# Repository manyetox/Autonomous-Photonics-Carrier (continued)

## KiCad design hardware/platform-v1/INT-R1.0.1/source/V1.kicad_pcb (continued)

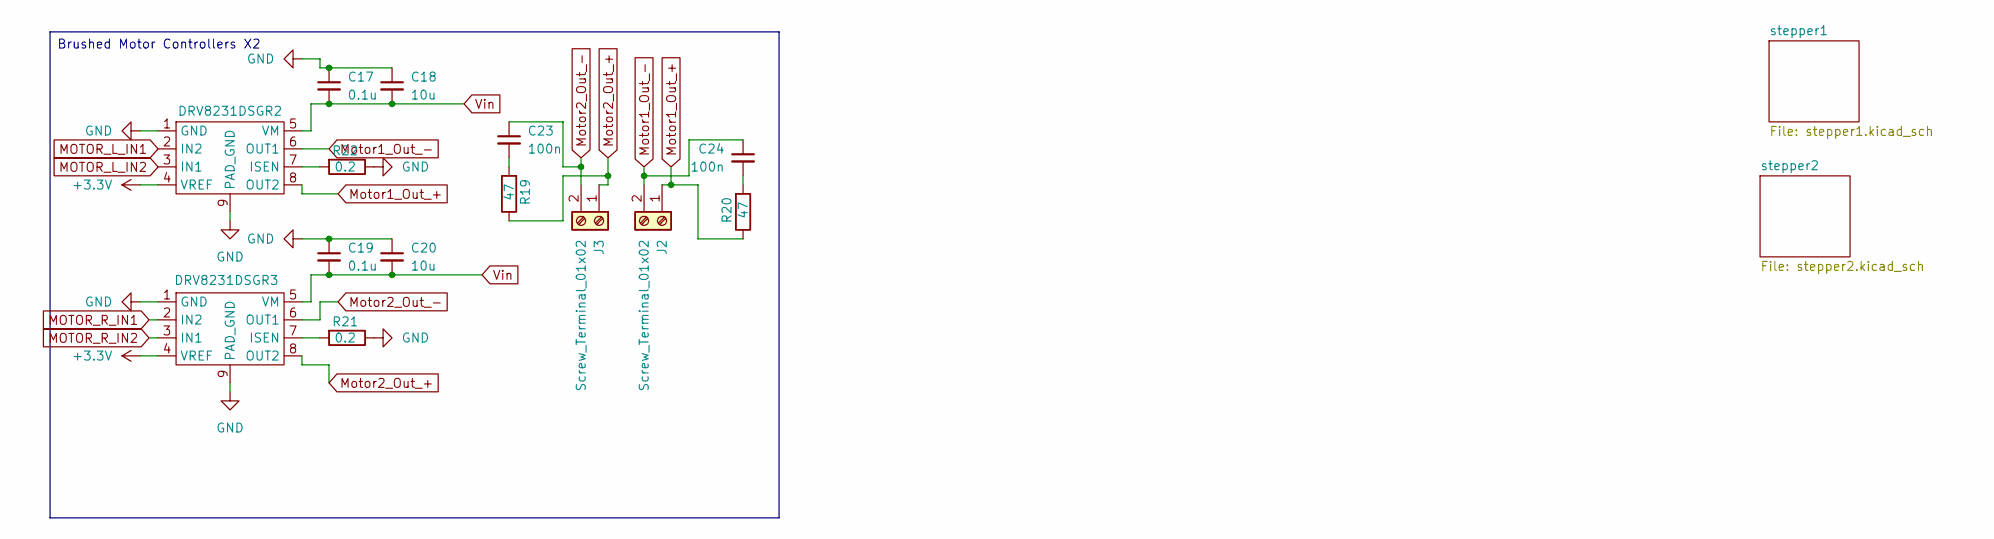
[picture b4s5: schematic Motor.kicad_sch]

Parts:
C17, C19: 0.1u; C_0402_1005Metric_Pad0.74x0.62mm_HandSolder; LCSC Part # C14663
C18, C20: 10u; C_0603_1608Metric_Pad1.08x0.95mm_HandSolder; LCSC Part # C5464883
C23, C24: 100n; C_0402_1005Metric_Pad0.74x0.62mm_HandSolder; LCSC Part # C14663
DRV8231DSGR2, DRV8231DSGR3: HSOP-8-1EP_3.9x4.9mm_P1.27mm_EP2.41x3.1mm_ThermalVias; LCSC Part # C3681197
J2: Screw_Terminal_01x02; PinHeader_2x01_P2.54mm_Vertical
J3: Screw_Terminal_01x02; PinSocket_2x01_P2.54mm_Vertical
R19, R20: 47; R_1206_3216Metric_Pad1.30x1.75mm_HandSolder; LCSC Part # C23182
R21, R22: 0.2; R_2512_6332Metric_Pad1.40x3.35mm_HandSolder; LCSC Part # C23182

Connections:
GND: C17.1, C18.1, C19.1, C20.1, DRV8231DSGR2.1 (GND), DRV8231DSGR2.9 (PAD_GND), DRV8231DSGR3.1 (GND), DRV8231DSGR3.9 (PAD_GND), R21.1, R22.1; also elsewhere on the board
MOTOR_L_IN1: DRV8231DSGR2.2 (IN2); also elsewhere on the board
MOTOR_L_IN2: DRV8231DSGR2.3 (IN1); also elsewhere on the board
MOTOR_R_IN1: DRV8231DSGR3.2 (IN2); also elsewhere on the board
MOTOR_R_IN2: DRV8231DSGR3.3 (IN1); also elsewhere on the board
Motor1_Out_+: DRV8231DSGR2.8 (OUT2), J2.1, R20.1
Motor1_Out_-: C24.1, DRV8231DSGR2.6 (OUT1), J2.2
Motor2_Out_+: DRV8231DSGR3.8 (OUT2), J3.1, R19.1
Motor2_Out_-: C23.1, DRV8231DSGR3.6 (OUT1), J3.2
unnamed: C23.2, R19.2
unnamed: C24.2, R20.2
unnamed: DRV8231DSGR2.7 (ISEN), R22.2
unnamed: DRV8231DSGR3.7 (ISEN), R21.2
PS1: DRV8231DSGR2.4 (VREF), DRV8231DSGR3.4 (VREF); also elsewhere on the board
Vin: C17.2, C18.2, C19.2, C20.2, DRV8231DSGR2.5 (VM), DRV8231DSGR3.5 (VM); also elsewhere on the board

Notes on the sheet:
Brushed Motor Controllers X2

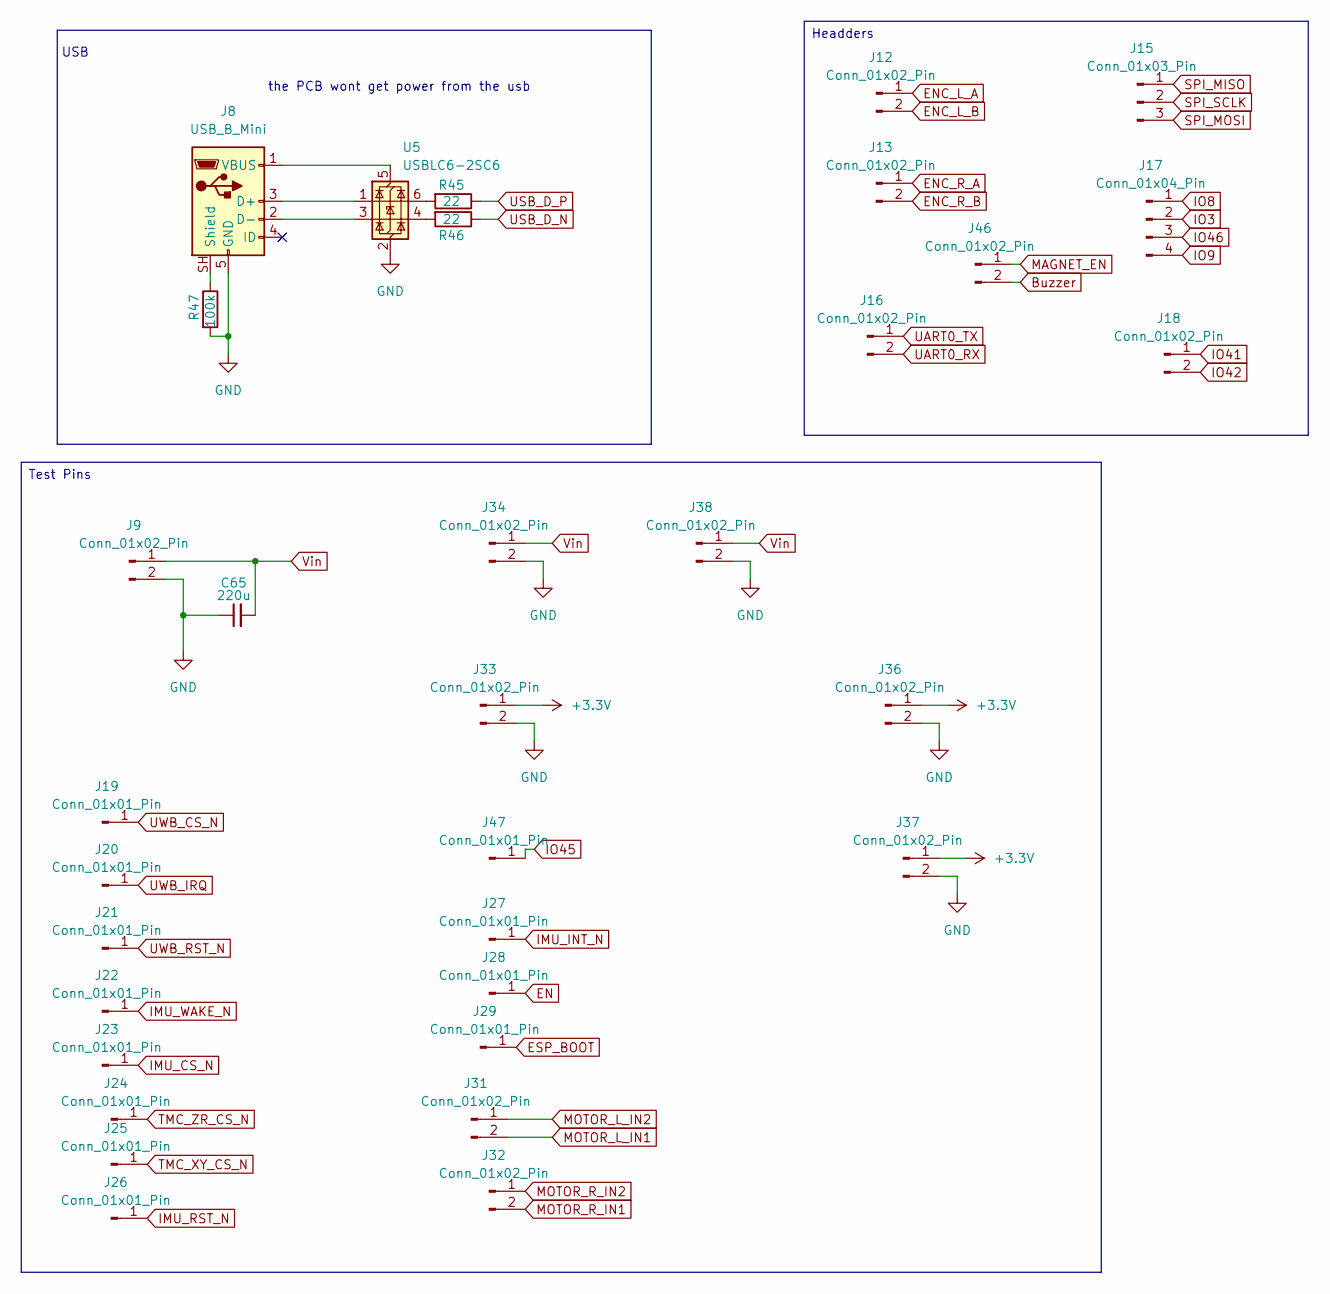
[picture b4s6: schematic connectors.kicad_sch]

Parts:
C65: 220u; C_Radial_D10.0mm_H12.5mm_P5.00mm; LCSC Part # C14663
J8: USB_B_Mini; USB_Mini-B_Wuerth_65100516121_Horizontal
J9, J12, J13, J16, J18, J31, J32, J33, J34, J36, J37, J46: Conn_01x02_Pin; PinHeader_1x02_P1.00mm_Vertical
J15: Conn_01x03_Pin; PinHeader_1x03_P1.00mm_Vertical
J17: Conn_01x04_Pin; PinHeader_1x04_P1.00mm_Vertical
J19, J20, J21, J22, J23, J24, J25, J26, J27, J28, J29, J47: Conn_01x01_Pin; SolderWirePad_1x01_SMD_1x2mm
J38: Conn_01x02_Pin; PinHeader_1x02_P2.54mm_Vertical
R45, R46: 22; R_0402_1005Metric_Pad0.72x0.64mm_HandSolder; LCSC Part # C4211
R47: 100k; R_0402_1005Metric_Pad0.72x0.64mm_HandSolder; LCSC Part # C4211
U5: USBLC6-2SC6; SOT-23-6

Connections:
Buzzer: J46.2; also elsewhere on the board
EN: J28.1 (Pin_1_1); also elsewhere on the board
ENC_L_A: J12.1; also elsewhere on the board
ENC_L_B: J12.2; also elsewhere on the board
ENC_R_A: J13.1; also elsewhere on the board
ENC_R_B: J13.2; also elsewhere on the board
ESP_BOOT: J29.1 (Pin_1_1); also elsewhere on the board
GND: C65.1, J8.5 (GND), J9.2, J33.2, J34.2, J36.2, J37.2, J38.2, R47.2, U5.2 (GND); also elsewhere on the board
IMU_CS_N: J23.1 (Pin_1_1); also elsewhere on the board
IMU_INT_N: J27.1 (Pin_1_1); also elsewhere on the board
IMU_RST_N: J26.1 (Pin_1_1); also elsewhere on the board
IMU_WAKE_N: J22.1 (Pin_1_1); also elsewhere on the board
IO3: J17.2; also elsewhere on the board
IO8: J17.1; also elsewhere on the board
IO9: J17.4; also elsewhere on the board
IO41: J18.1; also elsewhere on the board
IO42: J18.2; also elsewhere on the board
IO45: J47.1 (Pin_1_1); also elsewhere on the board
IO46: J17.3; also elsewhere on the board
MAGNET_EN: J46.1; also elsewhere on the board
MOTOR_L_IN1: J31.2; also elsewhere on the board
MOTOR_L_IN2: J31.1; also elsewhere on the board
MOTOR_R_IN1: J32.2; also elsewhere on the board
MOTOR_R_IN2: J32.1; also elsewhere on the board
unnamed: J8.3 (D+), U5.1 (I/O1)
unnamed: J8.2 (D-), U5.3 (I/O2)
unnamed: J8.SH (Shield), R47.1
unnamed: J8.1 (VBUS), U5.5 (VBUS)
unnamed: R45.2, U5.6 (I/O1)
unnamed: R46.2, U5.4 (I/O2)
PS1: J33.1, J36.1, J37.1; also elsewhere on the board
SPI_MISO: J15.1; also elsewhere on the board
SPI_MOSI: J15.3; also elsewhere on the board
SPI_SCLK: J15.2; also elsewhere on the board
TMC_XY_CS_N: J25.1 (Pin_1_1); also elsewhere on the board
TMC_ZR_CS_N: J24.1 (Pin_1_1); also elsewhere on the board
UART0_RX: J16.2; also elsewhere on the board
UART0_TX: J16.1; also elsewhere on the board
USB_D_N: R46.1; also elsewhere on the board
USB_D_P: R45.1; also elsewhere on the board
UWB_CS_N: J19.1 (Pin_1_1); also elsewhere on the board
UWB_IRQ: J20.1 (Pin_1_1); also elsewhere on the board
UWB_RST_N: J21.1 (Pin_1_1); also elsewhere on the board
Vin: C65.2, J9.1, J34.1, J38.1; also elsewhere on the board

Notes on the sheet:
USB
the PCB wont get power from the usb
Test Pins
Headders

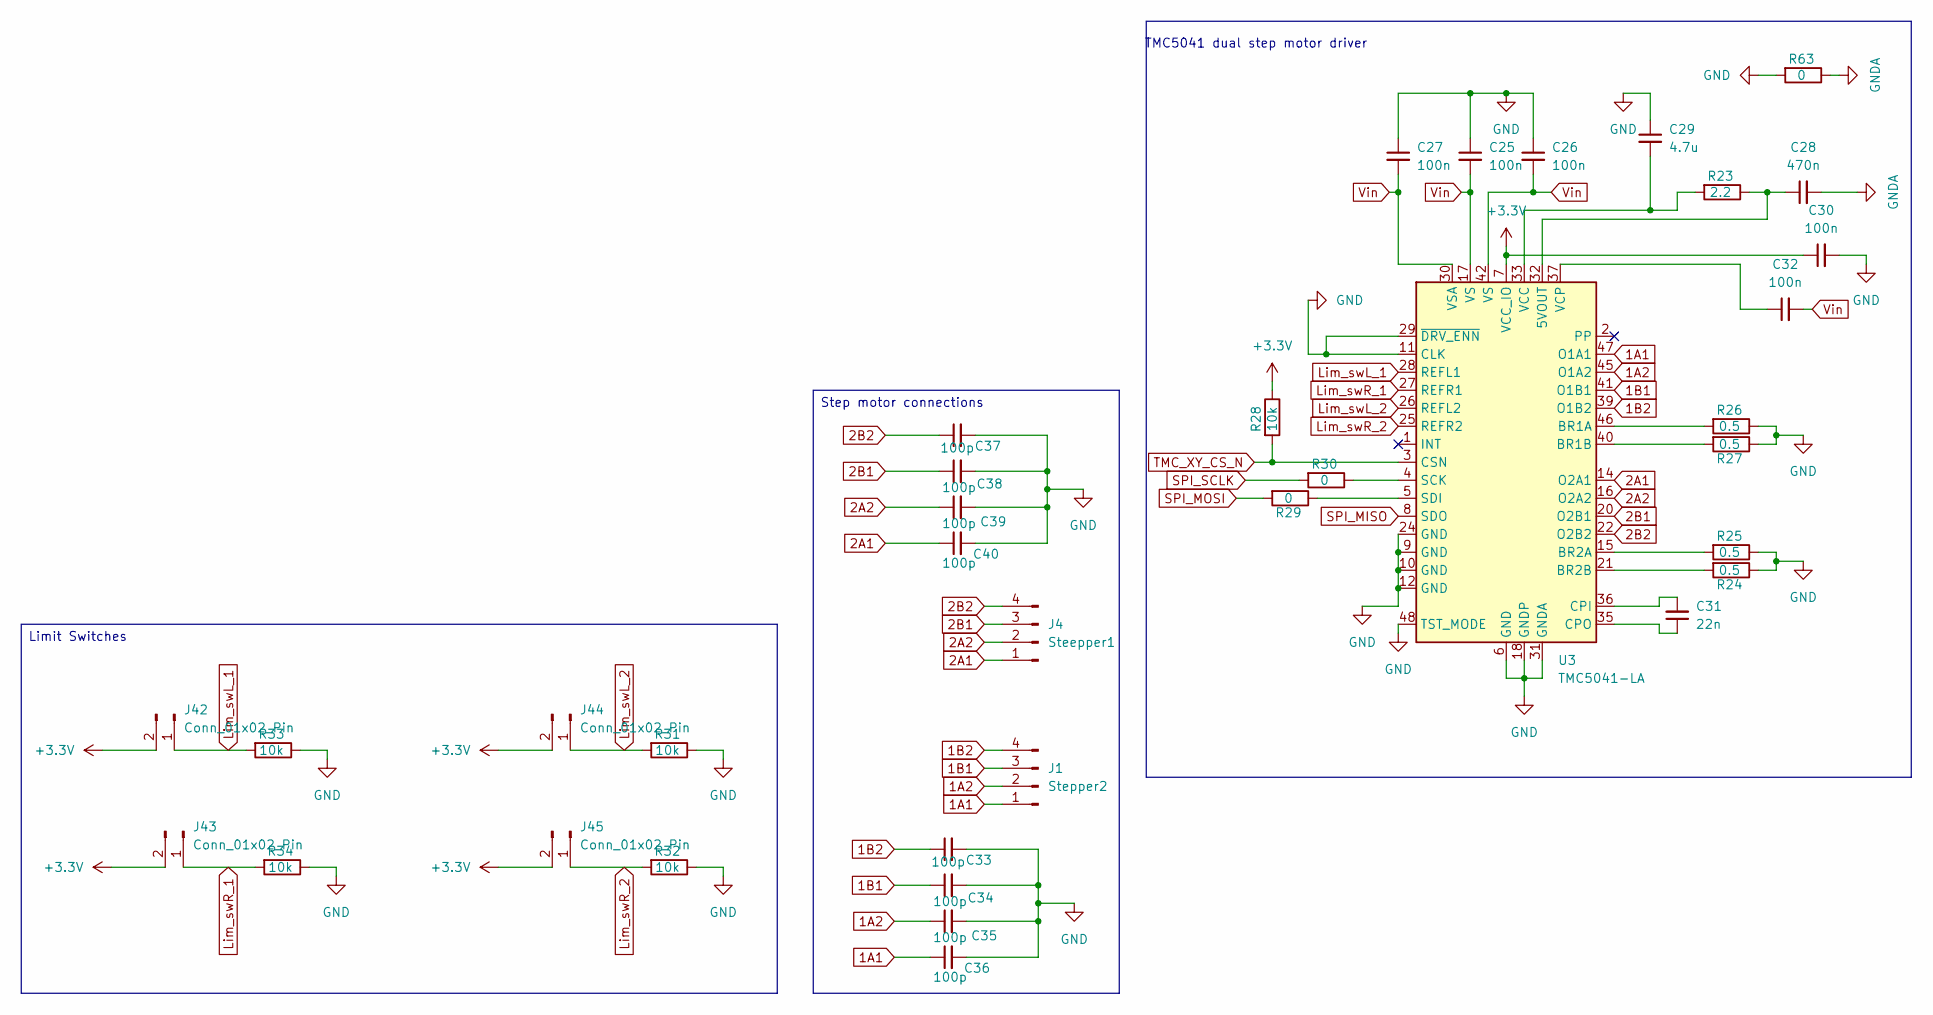
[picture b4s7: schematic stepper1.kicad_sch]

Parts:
C25, C26, C27, C30, C32: 100n; C_0402_1005Metric_Pad0.74x0.62mm_HandSolder; LCSC Part # C14663
C28: 470n; C_0402_1005Metric_Pad0.74x0.62mm_HandSolder; LCSC Part # C14663
C29: 4.7u; C_0402_1005Metric_Pad0.74x0.62mm_HandSolder; LCSC Part # C14663
C31: 22n; C_0402_1005Metric_Pad0.74x0.62mm_HandSolder; LCSC Part # C14663
C33, C34, C35, C36, C37, C38, C39, C40: 100p; C_0402_1005Metric_Pad0.74x0.62mm_HandSolder; LCSC Part # C14663
J1: Stepper2; PinHeader_1x04_P1.00mm_Vertical
J4: Steepper1; PinHeader_1x04_P1.00mm_Vertical
J42, J43, J44, J45: Conn_01x02_Pin; PinHeader_1x02_P1.00mm_Vertical
R23: 2.2; R_0402_1005Metric_Pad0.72x0.64mm_HandSolder; LCSC Part # C23182
R24, R25, R26, R27: 0.5; R_1206_3216Metric_Pad1.30x1.75mm_HandSolder; LCSC Part # C23182
R28, R31, R32, R33, R34: 10k; R_0402_1005Metric_Pad0.72x0.64mm_HandSolder; LCSC Part # C23182
R29, R30, R63: 0; R_0402_1005Metric_Pad0.72x0.64mm_HandSolder; LCSC Part # C23182
U3: TMC5041-LA; QFN-48-1EP_7x7mm_P0.5mm_EP5.3x5.3mm_ThermalVias

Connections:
1A1: C36.1, J1.1, U3.47 (O1A1)
1A2: C35.1, J1.2, U3.45 (O1A2)
1B1: C34.1, J1.3, U3.41 (O1B1)
1B2: C33.1, J1.4, U3.39 (O1B2)
2A1: C40.1, J4.1, U3.14 (O2A1)
2A2: C39.1, J4.2, U3.16 (O2A2)
2B1: C38.1, J4.3, U3.20 (O2B1)
2B2: C37.1, J4.4, U3.22 (O2B2)
GND: C25.1, C26.1, C27.1, C29.1, C30.2, C33.2, C34.2, C35.2, C36.2, C37.2, C38.2, C39.2, C40.2, R24.1, R25.1, R26.1, R27.1, R31.1, R32.1, R33.1, R34.1, R63.2, U3.6 (GND), U3.9 (GND), U3.10 (GND), U3.11 (CLK), U3.12 (GND), U3.13 (nc), U3.18 (GNDP), U3.23 (nc), U3.24 (GND), U3.29 (~DRV_ENN), U3.31 (GNDA), U3.34 (GND), U3.38 (nc), U3.43 (GNDP), U3.48 (TST_MODE), U3.49 (EP_GND); also elsewhere on the board
GNDA: C28.2, R63.1; also elsewhere on the board
Lim_swL_1: J42.1, R33.2, U3.28 (REFL1)
Lim_swL_2: J44.1, R31.2, U3.26 (REFL2)
Lim_swR_1: J43.1, R34.2, U3.27 (REFR1)
Lim_swR_2: J45.1, R32.2, U3.25 (REFR2)
unnamed: C28.1, R23.1, U3.32 (5VOUT)
unnamed: R26.2, U3.46 (BR1A)
unnamed: R27.2, U3.40 (BR1B)
unnamed: R25.2, U3.15 (BR2A)
unnamed: R24.2, U3.21 (BR2B)
unnamed: C31.2, U3.36 (CPI)
unnamed: C31.1, U3.35 (CPO)
unnamed: R30.1, U3.4 (SCK)
unnamed: R29.1, U3.5 (SDI)
unnamed: C29.2, R23.2, U3.33 (VCC)
unnamed: C32.1, U3.37 (VCP)
PS1: C30.1, J42.2, J43.2, J44.2, J45.2, R28.1, U3.7 (VCC_IO); also elsewhere on the board
SPI_MISO: U3.8 (SDO); also elsewhere on the board
SPI_MOSI: R29.2; also elsewhere on the board
SPI_SCLK: R30.2; also elsewhere on the board
TMC_XY_CS_N: R28.2, U3.3 (CSN); also elsewhere on the board
Vin: C25.2, C26.2, C27.2, C32.2, U3.17 (VS), U3.19 (VS), U3.30 (VSA), U3.42 (VS), U3.44 (VS); also elsewhere on the board

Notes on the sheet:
TMC5041 dual step motor driver
Limit Switches
Step motor connections

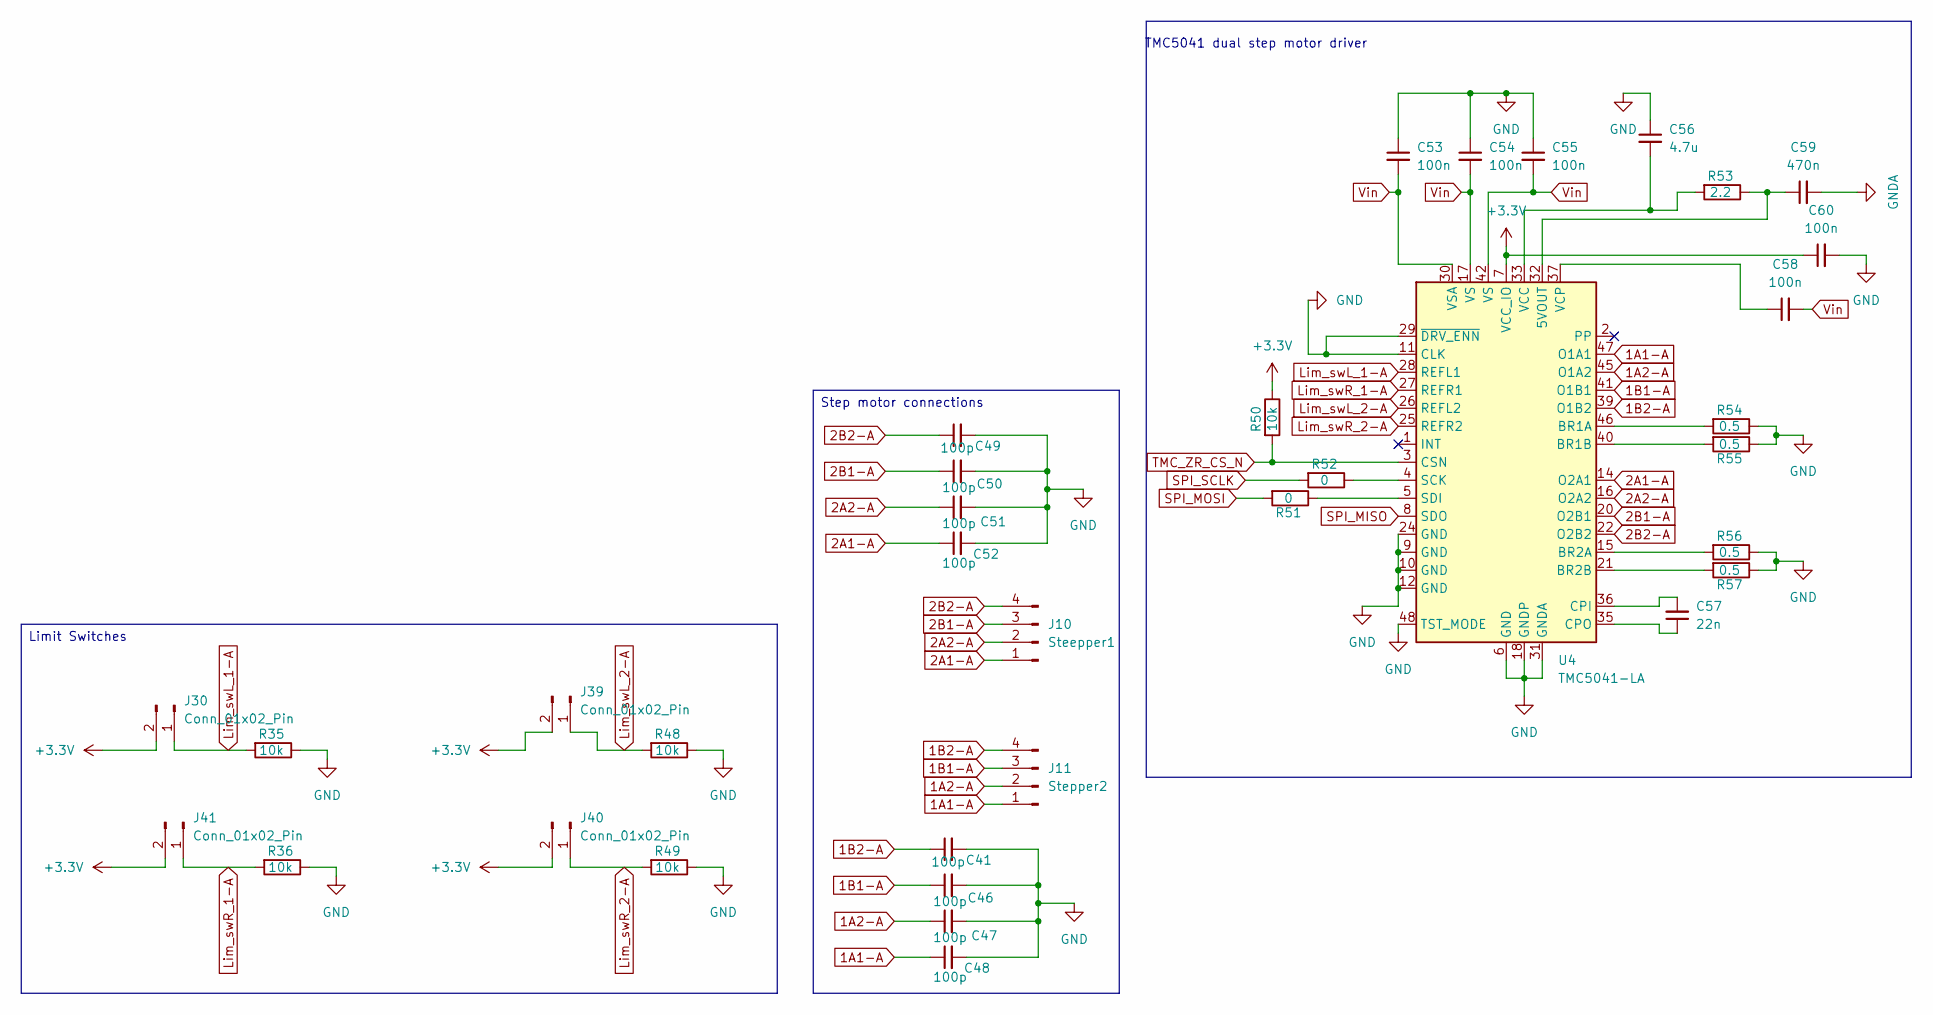
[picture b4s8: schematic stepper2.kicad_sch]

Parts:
C41, C46, C47, C48, C49, C50, C51, C52: 100p; C_0402_1005Metric_Pad0.74x0.62mm_HandSolder; LCSC Part # C14663
C53, C54, C55, C58, C60: 100n; C_0402_1005Metric_Pad0.74x0.62mm_HandSolder; LCSC Part # C14663
C56: 4.7u; C_0402_1005Metric_Pad0.74x0.62mm_HandSolder; LCSC Part # C14663
C57: 22n; C_0402_1005Metric_Pad0.74x0.62mm_HandSolder; LCSC Part # C14663
C59: 470n; C_0402_1005Metric_Pad0.74x0.62mm_HandSolder; LCSC Part # C14663
J10: Steepper1; PinHeader_1x04_P1.00mm_Vertical
J11: Stepper2; PinHeader_1x04_P1.00mm_Vertical
J30, J39, J40, J41: Conn_01x02_Pin; PinHeader_1x02_P1.00mm_Vertical
R35, R36, R48, R49, R50: 10k; R_0402_1005Metric_Pad0.72x0.64mm_HandSolder; LCSC Part # C23182
R51, R52: 0; R_0402_1005Metric_Pad0.72x0.64mm_HandSolder; LCSC Part # C23182
R53: 2.2; R_0402_1005Metric_Pad0.72x0.64mm_HandSolder; LCSC Part # C23182
R54, R55, R56, R57: 0.5; R_1206_3216Metric_Pad1.30x1.75mm_HandSolder; LCSC Part # C23182
U4: TMC5041-LA; QFN-48-1EP_7x7mm_P0.5mm_EP5.3x5.3mm_ThermalVias

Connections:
1A1-A: C48.1, J11.1, U4.47 (O1A1)
1A2-A: C47.1, J11.2, U4.45 (O1A2)
1B1-A: C46.1, J11.3, U4.41 (O1B1)
1B2-A: C41.1, J11.4, U4.39 (O1B2)
2A1-A: C52.1, J10.1, U4.14 (O2A1)
2A2-A: C51.1, J10.2, U4.16 (O2A2)
2B1-A: C50.1, J10.3, U4.20 (O2B1)
2B2-A: C49.1, J10.4, U4.22 (O2B2)
GND: C41.2, C46.2, C47.2, C48.2, C49.2, C50.2, C51.2, C52.2, C53.1, C54.1, C55.1, C56.1, C60.2, R35.1, R36.1, R48.1, R49.1, R54.1, R55.1, R56.1, R57.1, U4.6 (GND), U4.9 (GND), U4.10 (GND), U4.11 (CLK), U4.12 (GND), U4.13 (nc), U4.18 (GNDP), U4.23 (nc), U4.24 (GND), U4.29 (~DRV_ENN), U4.31 (GNDA), U4.34 (GND), U4.38 (nc), U4.43 (GNDP), U4.48 (TST_MODE), U4.49 (EP_GND); also elsewhere on the board
GNDA: C59.2; also elsewhere on the board
Lim_swL_1-A: J30.1, R35.2, U4.28 (REFL1)
Lim_swL_2-A: J39.1, R48.2, U4.26 (REFL2)
Lim_swR_1-A: J41.1, R36.2, U4.27 (REFR1)
Lim_swR_2-A: J40.1, R49.2, U4.25 (REFR2)
unnamed: C59.1, R53.1, U4.32 (5VOUT)
unnamed: R54.2, U4.46 (BR1A)
unnamed: R55.2, U4.40 (BR1B)
unnamed: R56.2, U4.15 (BR2A)
unnamed: R57.2, U4.21 (BR2B)
unnamed: C57.2, U4.36 (CPI)
unnamed: C57.1, U4.35 (CPO)
unnamed: R52.1, U4.4 (SCK)
unnamed: R51.1, U4.5 (SDI)
unnamed: C56.2, R53.2, U4.33 (VCC)
unnamed: C58.1, U4.37 (VCP)
PS1: C60.1, J30.2, J39.2, J40.2, J41.2, R50.1, U4.7 (VCC_IO); also elsewhere on the board
SPI_MISO: U4.8 (SDO); also elsewhere on the board
SPI_MOSI: R51.2; also elsewhere on the board
SPI_SCLK: R52.2; also elsewhere on the board
TMC_ZR_CS_N: R50.2, U4.3 (CSN); also elsewhere on the board
Vin: C53.2, C54.2, C55.2, C58.2, U4.17 (VS), U4.19 (VS), U4.30 (VSA), U4.42 (VS), U4.44 (VS); also elsewhere on the board

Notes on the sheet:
TMC5041 dual step motor driver
Limit Switches
Step motor connections

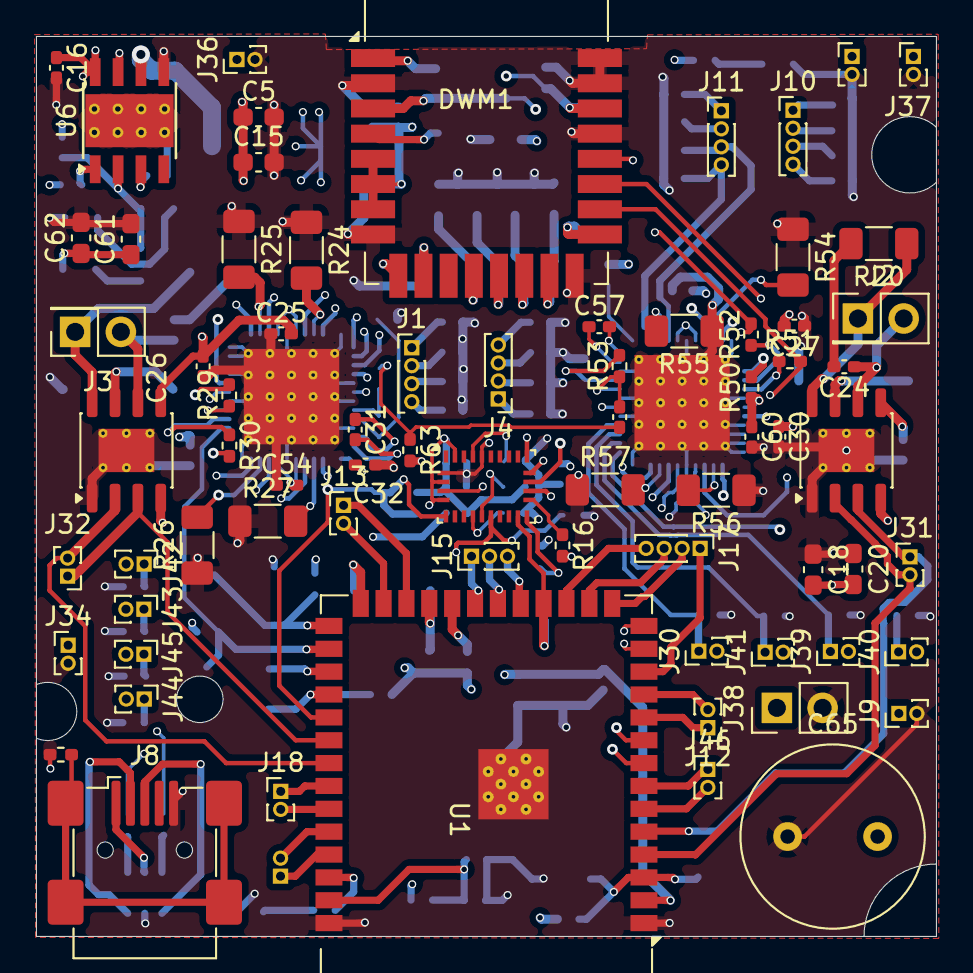
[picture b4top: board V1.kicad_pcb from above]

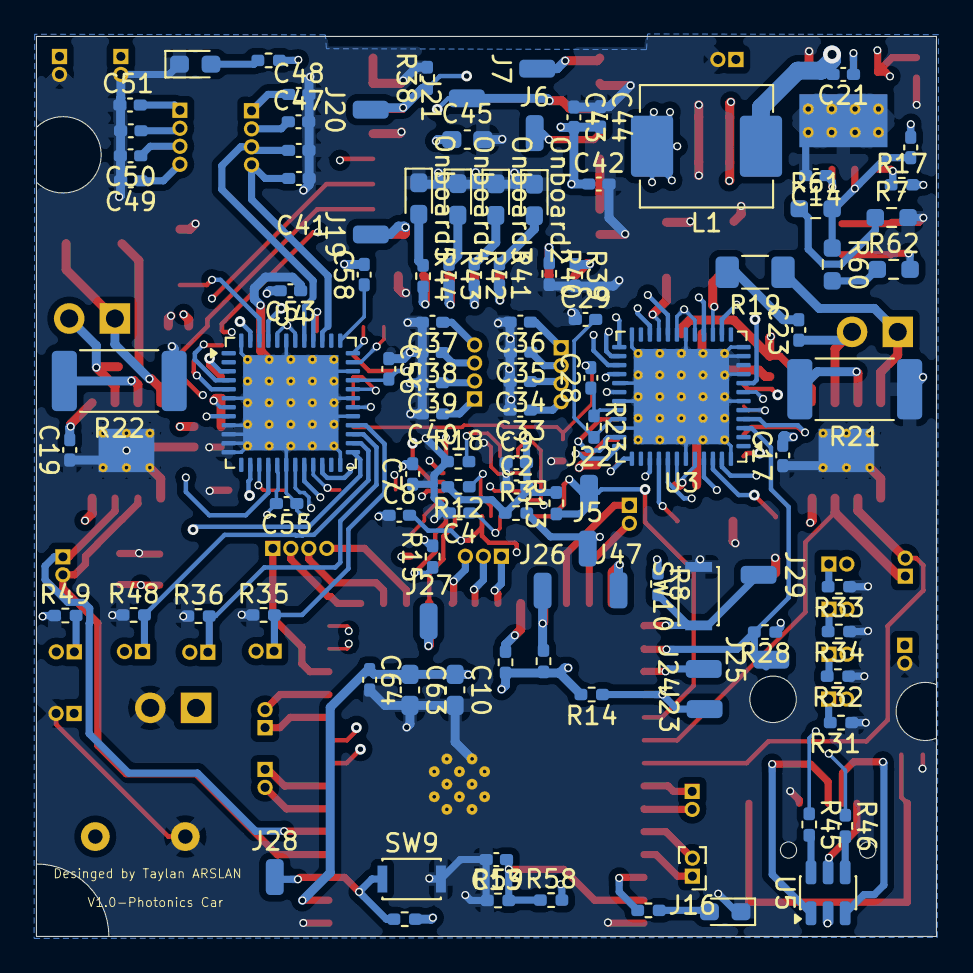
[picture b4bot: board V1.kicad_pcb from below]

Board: 8 copper layers, 50.0 x 50.0 mm, 182 parts (110 on the bottom side), 128 nets.

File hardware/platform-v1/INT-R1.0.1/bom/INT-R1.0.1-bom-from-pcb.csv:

Quantity,References,Value / Part,Footprint,Source
5,"R29, R30, R51, R52, R63",0,Resistor_SMD:R_0402_1005Metric_Pad0.72x0.64mm_HandSolder,Auto-extracted from KiCad PCB; verify against schematic before ordering
2,"R62, R7",0,Resistor_SMD:R_0603_1608Metric_Pad0.98x0.95mm_HandSolder,Auto-extracted from KiCad PCB; verify against schematic before ordering
4,"C13, C17, C19, C21",0.1u,Capacitor_SMD:C_0402_1005Metric_Pad0.74x0.62mm_HandSolder,Auto-extracted from KiCad PCB; verify against schematic before ordering
4,"C4, C7, C8, C9",0.1uF,Capacitor_SMD:C_0402_1005Metric_Pad0.74x0.62mm_HandSolder,Auto-extracted from KiCad PCB; verify against schematic before ordering
2,"R21, R22",0.2,Resistor_SMD:R_2512_6332Metric_Pad1.40x3.35mm_HandSolder,Auto-extracted from KiCad PCB; verify against schematic before ordering
1,C14,0.47u,Capacitor_SMD:C_0402_1005Metric_Pad0.74x0.62mm_HandSolder,Auto-extracted from KiCad PCB; verify against schematic before ordering
8,"R24, R25, R26, R27, R54, R55, R56, R57",0.5,Resistor_SMD:R_1206_3216Metric_Pad1.30x1.75mm_HandSolder,Auto-extracted from KiCad PCB; verify against schematic before ordering
4,"R38, R39, R40, R47",100k,Resistor_SMD:R_0402_1005Metric_Pad0.72x0.64mm_HandSolder,Auto-extracted from KiCad PCB; verify against schematic before ordering
17,"C16, C23, C24, C25, C26, C27, C30, C32, C42, C43, C44, C53, C54, C55, C58, C60, C64",100n,Capacitor_SMD:C_0402_1005Metric_Pad0.74x0.62mm_HandSolder,Auto-extracted from KiCad PCB; verify against schematic before ordering
16,"C33, C34, C35, C36, C37, C38, C39, C40, C41, C46, C47, C48, C49, C50, C51, C52",100p,Capacitor_SMD:C_0402_1005Metric_Pad0.74x0.62mm_HandSolder,Auto-extracted from KiCad PCB; verify against schematic before ordering
19,"R1, R12, R13, R14, R18, R28, R3, R31, R32, R33, R34, R35, R36, R37, R4, R48, R49, R50, R8",10k,Resistor_SMD:R_0402_1005Metric_Pad0.72x0.64mm_HandSolder,Auto-extracted from KiCad PCB; verify against schematic before ordering
7,"C10, C15, C18, C20, C45, C5, C63",10u,Capacitor_SMD:C_0603_1608Metric_Pad1.08x0.95mm_HandSolder,Auto-extracted from KiCad PCB; verify against schematic before ordering
1,R60,150K,Resistor_SMD:R_0603_1608Metric_Pad0.98x0.95mm_HandSolder,Auto-extracted from KiCad PCB; verify against schematic before ordering
2,"R10, R17",1k,Resistor_SMD:R_0402_1005Metric_Pad0.72x0.64mm_HandSolder,Auto-extracted from KiCad PCB; verify against schematic before ordering
2,"R23, R53",2.2,Resistor_SMD:R_0402_1005Metric_Pad0.72x0.64mm_HandSolder,Auto-extracted from KiCad PCB; verify against schematic before ordering
2,"R45, R46",22,Resistor_SMD:R_0402_1005Metric_Pad0.72x0.64mm_HandSolder,Auto-extracted from KiCad PCB; verify against schematic before ordering
1,C65,220u,Capacitor_THT:C_Radial_D10.0mm_H12.5mm_P5.00mm,Auto-extracted from KiCad PCB; verify against schematic before ordering
2,"C31, C57",22n,Capacitor_SMD:C_0402_1005Metric_Pad0.74x0.62mm_HandSolder,Auto-extracted from KiCad PCB; verify against schematic before ordering
2,"C61, C62",22u,Capacitor_SMD:C_0603_1608Metric_Pad1.08x0.95mm_HandSolder,Auto-extracted from KiCad PCB; verify against schematic before ordering
1,R58,250K,Resistor_SMD:R_0402_1005Metric_Pad0.72x0.64mm_HandSolder,Auto-extracted from KiCad PCB; verify against schematic before ordering
1,L1,3.3u,Inductor_SMD:L_Abracon_ASPI-0630LR,Auto-extracted from KiCad PCB; verify against schematic before ordering
1,R61,33k,Resistor_SMD:R_0603_1608Metric_Pad0.98x0.95mm_HandSolder,Auto-extracted from KiCad PCB; verify against schematic before ordering
5,"R11, R41, R42, R43, R44",3k,Resistor_SMD:R_0402_1005Metric_Pad0.72x0.64mm_HandSolder,Auto-extracted from KiCad PCB; verify against schematic before ordering
2,"R15, R16",4.7k,Resistor_SMD:R_0402_1005Metric_Pad0.72x0.64mm_HandSolder,Auto-extracted from KiCad PCB; verify against schematic before ordering
2,"C29, C56",4.7u,Capacitor_SMD:C_0402_1005Metric_Pad0.74x0.62mm_HandSolder,Auto-extracted from KiCad PCB; verify against schematic before ordering
1,C2,4.7uF,Capacitor_SMD:C_0402_1005Metric_Pad0.74x0.62mm_HandSolder,Auto-extracted from KiCad PCB; verify against schematic before ordering
2,"R19, R20",47,Resistor_SMD:R_1206_3216Metric_Pad1.30x1.75mm_HandSolder,Auto-extracted from KiCad PCB; verify against schematic before ordering
2,"C28, C59",470n,Capacitor_SMD:C_0402_1005Metric_Pad0.74x0.62mm_HandSolder,Auto-extracted from KiCad PCB; verify against schematic before ordering
1,R59,53K,Resistor_SMD:R_0402_1005Metric_Pad0.72x0.64mm_HandSolder,Auto-extracted from KiCad PCB; verify against schematic before ordering
1,C22,5pf,Capacitor_SMD:C_0402_1005Metric_Pad0.74x0.62mm_HandSolder,Auto-extracted from KiCad PCB; verify against schematic before ordering
1,BMO1,BNO086,Package_LGA:LGA-28_5.2x3.8mm_P0.5mm,Auto-extracted from KiCad PCB; verify against schematic before ordering
1,J5,BNO_BOOT_Test_pin,Connector_Wire:SolderWirePad_1x01_SMD_1x2mm,Auto-extracted from KiCad PCB; verify against schematic before ordering
14,"J19, J20, J21, J22, J23, J24, J25, J26, J27, J28, J29, J47, J6, J7",Conn_01x01_Pin,Connector_Wire:SolderWirePad_1x01_SMD_1x2mm,Auto-extracted from KiCad PCB; verify against schematic before ordering
20,"J12, J13, J16, J18, J30, J31, J32, J33, J34, J36, J37, J39, J40, J41, J42, J43, J44, J45, J46, J9",Conn_01x02_Pin,Connector_PinHeader_1.00mm:PinHeader_1x02_P1.00mm_Vertical,Auto-extracted from KiCad PCB; verify against schematic before ordering
1,J38,Conn_01x02_Pin,Connector_PinHeader_2.54mm:PinHeader_1x02_P2.54mm_Vertical,Auto-extracted from KiCad PCB; verify against schematic before ordering
1,J15,Conn_01x03_Pin,Connector_PinHeader_1.00mm:PinHeader_1x03_P1.00mm_Vertical,Auto-extracted from KiCad PCB; verify against schematic before ordering
1,J17,Conn_01x04_Pin,Connector_PinHeader_1.00mm:PinHeader_1x04_P1.00mm_Vertical,Auto-extracted from KiCad PCB; verify against schematic before ordering
2,"DRV8231DSGR2, DRV8231DSGR3",DRV8231DSGR,Package_SO:HSOP-8-1EP_3.9x4.9mm_P1.27mm_EP2.41x3.1mm_ThermalVias,Auto-extracted from KiCad PCB; verify against schematic before ordering
1,DWM1,DWM3000,RF_Module:DWM1000,Auto-extracted from KiCad PCB; verify against schematic before ordering
1,U1,ESP32-S3-WROOM-1,RF_Module:ESP32-S3-WROOM-1,Auto-extracted from KiCad PCB; verify against schematic before ordering
6,"Onboard1, Onboard2, Onboard3, Onboard4, Onboard5, Outer1",LED,LED_SMD:LED_0603_1608Metric_Pad1.05x0.95mm_HandSolder,Auto-extracted from KiCad PCB; verify against schematic before ordering
2,"SW10, SW9",SW_Push,Button_Switch_SMD:SW_SPST_CK_KXT3,Auto-extracted from KiCad PCB; verify against schematic before ordering
1,J2,Screw_Terminal_01x02,Connector_PinHeader_2.54mm:PinHeader_2x01_P2.54mm_Vertical,Auto-extracted from KiCad PCB; verify against schematic before ordering
1,J3,Screw_Terminal_01x02,Connector_PinSocket_2.54mm:PinSocket_2x01_P2.54mm_Vertical,Auto-extracted from KiCad PCB; verify against schematic before ordering
2,"J10, J4",Steepper1,Connector_PinHeader_1.00mm:PinHeader_1x04_P1.00mm_Vertical,Auto-extracted from KiCad PCB; verify against schematic before ordering
2,"J1, J11",Stepper2,Connector_PinHeader_1.00mm:PinHeader_1x04_P1.00mm_Vertical,Auto-extracted from KiCad PCB; verify against schematic before ordering
2,"U3, U4",TMC5041-LA,Package_DFN_QFN:QFN-48-1EP_7x7mm_P0.5mm_EP5.3x5.3mm_ThermalVias,Auto-extracted from KiCad PCB; verify against schematic before ordering
1,U6,TPS56528DDA,Package_SO:Texas_HSOP-8-1EP_3.9x4.9mm_P1.27mm_ThermalVias,Auto-extracted from KiCad PCB; verify against schematic before ordering
1,U5,USBLC6-2SC6,Package_TO_SOT_SMD:SOT-23-6,Auto-extracted from KiCad PCB; verify against schematic before ordering
1,J8,USB_B_Mini,Connector_USB:USB_Mini-B_Wuerth_65100516121_Horizontal,Auto-extracted from KiCad PCB; verify against schematic before ordering

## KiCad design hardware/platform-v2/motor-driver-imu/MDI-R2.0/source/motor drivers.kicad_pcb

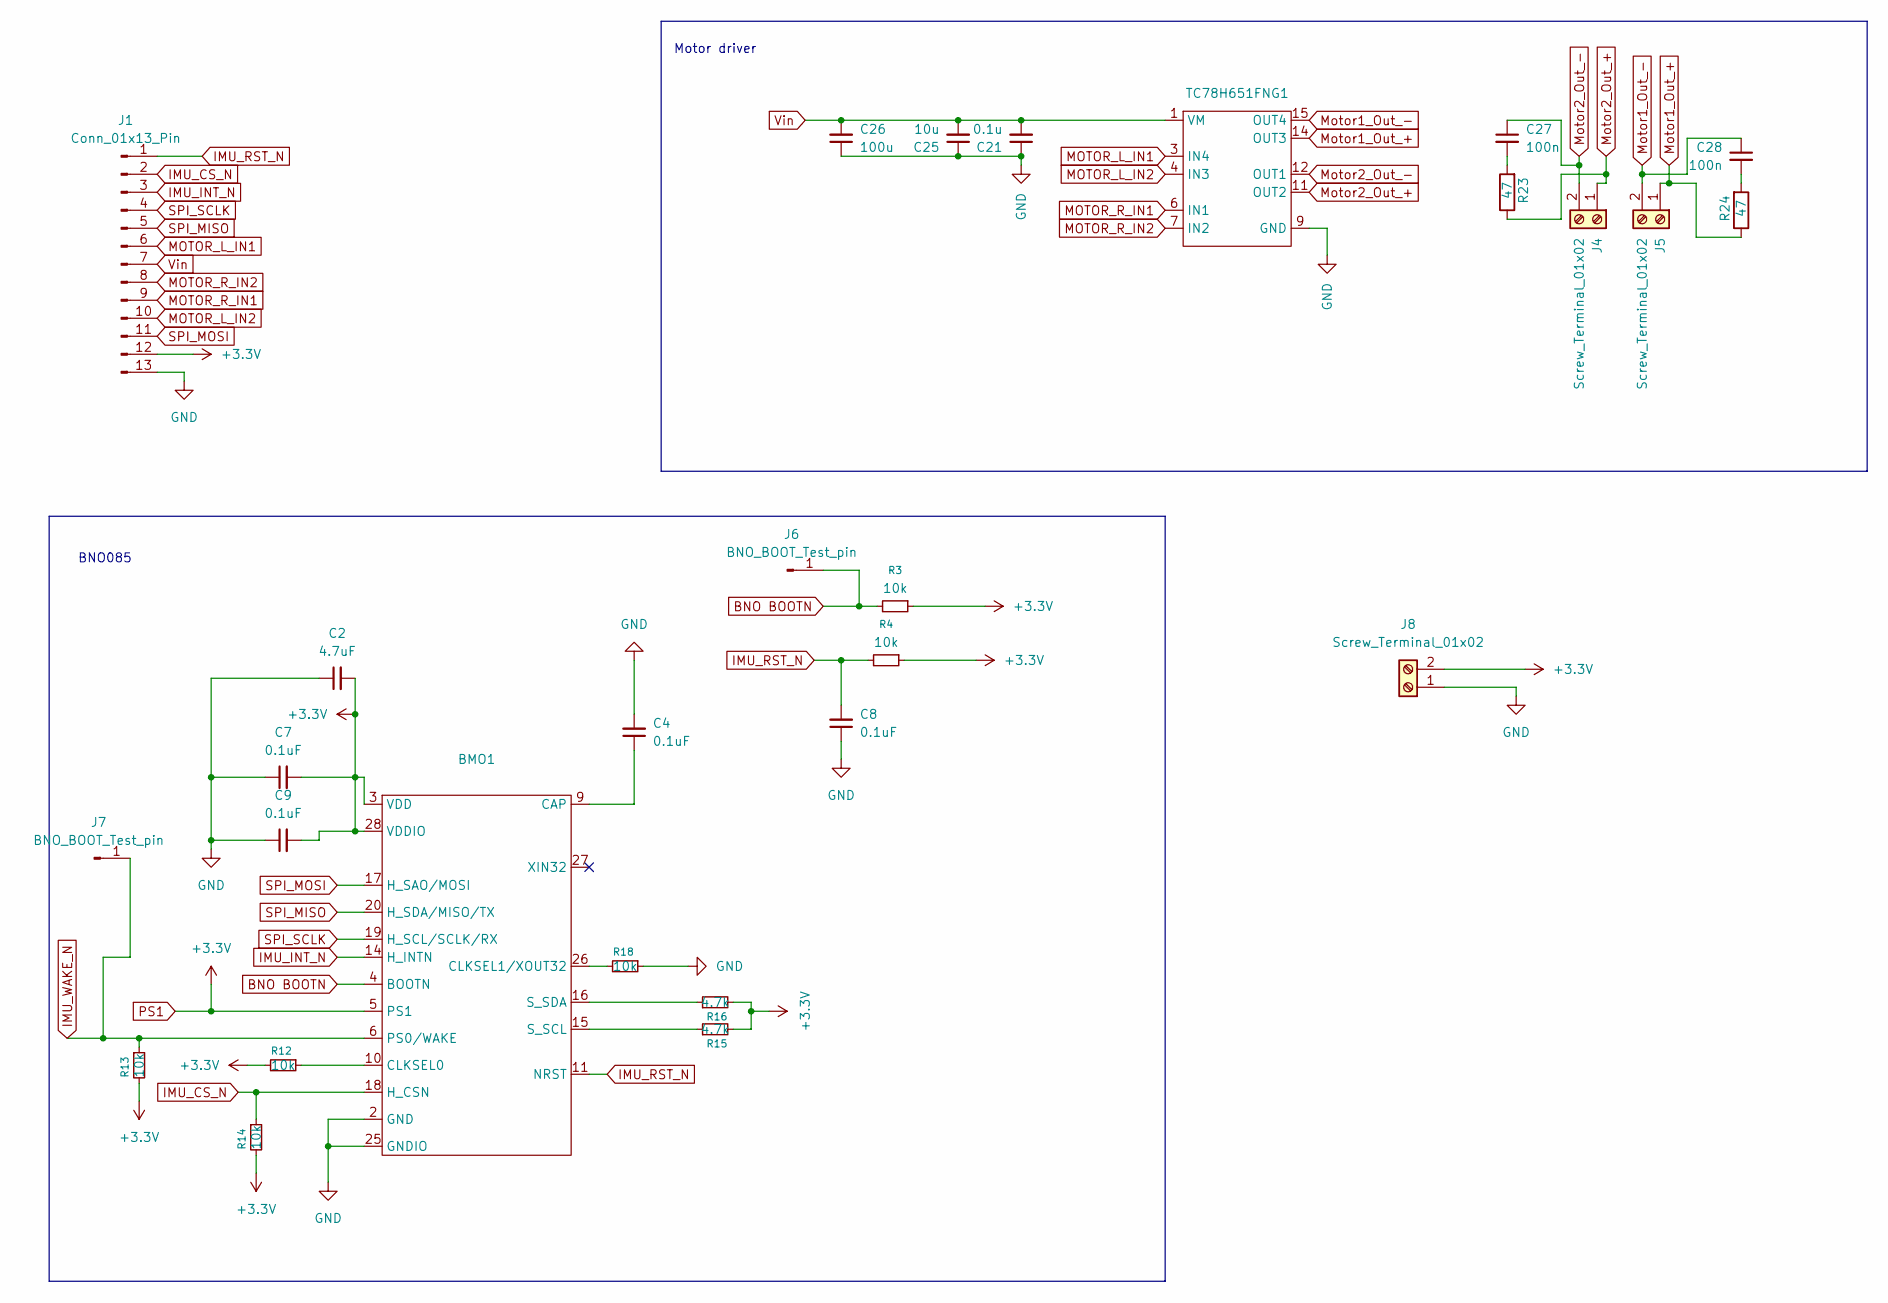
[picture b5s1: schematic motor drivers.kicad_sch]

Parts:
BMO1: LGA-28_5.2x3.8mm_P0.5mm
C2: 4.7uF; C_0805_2012Metric_Pad1.18x1.45mm_HandSolder
C4, C7, C8, C9: 0.1uF; C_0805_2012Metric_Pad1.18x1.45mm_HandSolder
C21: 0.1u; C_0805_2012Metric_Pad1.18x1.45mm_HandSolder; LCSC Part # C14663
C25: 10u; C_0805_2012Metric_Pad1.18x1.45mm_HandSolder; LCSC Part # C5464883
C26: 100u; C_1206_3216Metric_Pad1.33x1.80mm_HandSolder; LCSC Part # C5464883
C27, C28: 100n; C_0805_2012Metric_Pad1.18x1.45mm_HandSolder; LCSC Part # C14663
J1: Conn_01x13_Pin; 13-conn-smd-dual
J4, J5, J8: Screw_Terminal_01x02; power pad dual
J6, J7: BNO_BOOT_Test_pin; SolderWirePad_1x01_SMD_1x2mm
R3, R4, R12, R13, R14, R18: 10k; R_0603_1608Metric_Pad0.98x0.95mm_HandSolder
R15, R16: 4.7k; R_0603_1608Metric_Pad0.98x0.95mm_HandSolder
R23, R24: 47; R_1206_3216Metric_Pad1.30x1.75mm_HandSolder; LCSC Part # C23182
TC78H651FNG1: TSSOP-16_4.4x5mm_P0.65mm

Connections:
BNO BOOTN: BMO1.4 (BOOTN), J6.1 (Pin_1_1), R3.2
GND: BMO1.2 (GND), BMO1.25 (GNDIO), C2.1, C4.2, C7.1, C8.1, C9.1, C21.1, C25.1, C26.1, J1.13, J8.1, R18.1, TC78H651FNG1.9 (GND)
IMU_CS_N: BMO1.18 (H_CSN), J1.2, R14.1
IMU_INT_N: BMO1.14 (H_INTN), J1.3
IMU_RST_N: BMO1.11 (NRST), C8.2, J1.1, R4.2
IMU_WAKE_N: BMO1.6 (PS0/WAKE), J7.1 (Pin_1_1), R13.1
MOTOR_L_IN1: J1.6, TC78H651FNG1.3 (IN4)
MOTOR_L_IN2: J1.10, TC78H651FNG1.4 (IN3)
MOTOR_R_IN1: J1.9, TC78H651FNG1.6 (IN1)
MOTOR_R_IN2: J1.8, TC78H651FNG1.7 (IN2)
Motor1_Out_+: J5.1, R24.1, TC78H651FNG1.14 (OUT3)
Motor1_Out_-: C28.1, J5.2, TC78H651FNG1.15 (OUT4)
Motor2_Out_+: J4.1, R23.1, TC78H651FNG1.11 (OUT2)
Motor2_Out_-: C27.1, J4.2, TC78H651FNG1.12 (OUT1)
unnamed: BMO1.9 (CAP), C4.1
unnamed: BMO1.10 (CLKSEL0), R12.1
unnamed: BMO1.26 (CLKSEL1/XOUT32), R18.2
unnamed: BMO1.15 (S_SCL), R15.1
unnamed: BMO1.16 (S_SDA), R16.1
unnamed: C27.2, R23.2
unnamed: C28.2, R24.2
PS1: BMO1.3 (VDD), BMO1.5 (PS1), BMO1.8 (nc), BMO1.28 (VDDIO), C2.2, C7.2, C9.2, J1.12, J8.2, R3.1, R4.1, R12.2, R13.2, R14.2, R15.2, R16.2
SPI_MISO: BMO1.20 (H_SDA/MISO/TX), J1.5
SPI_MOSI: BMO1.17 (H_SAO/MOSI), J1.11
SPI_SCLK: BMO1.19 (H_SCL/SCLK/RX), J1.4
Vin: C21.2, C25.2, C26.2, J1.7, TC78H651FNG1.1 (VM)

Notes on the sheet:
BNO085
Motor driver
